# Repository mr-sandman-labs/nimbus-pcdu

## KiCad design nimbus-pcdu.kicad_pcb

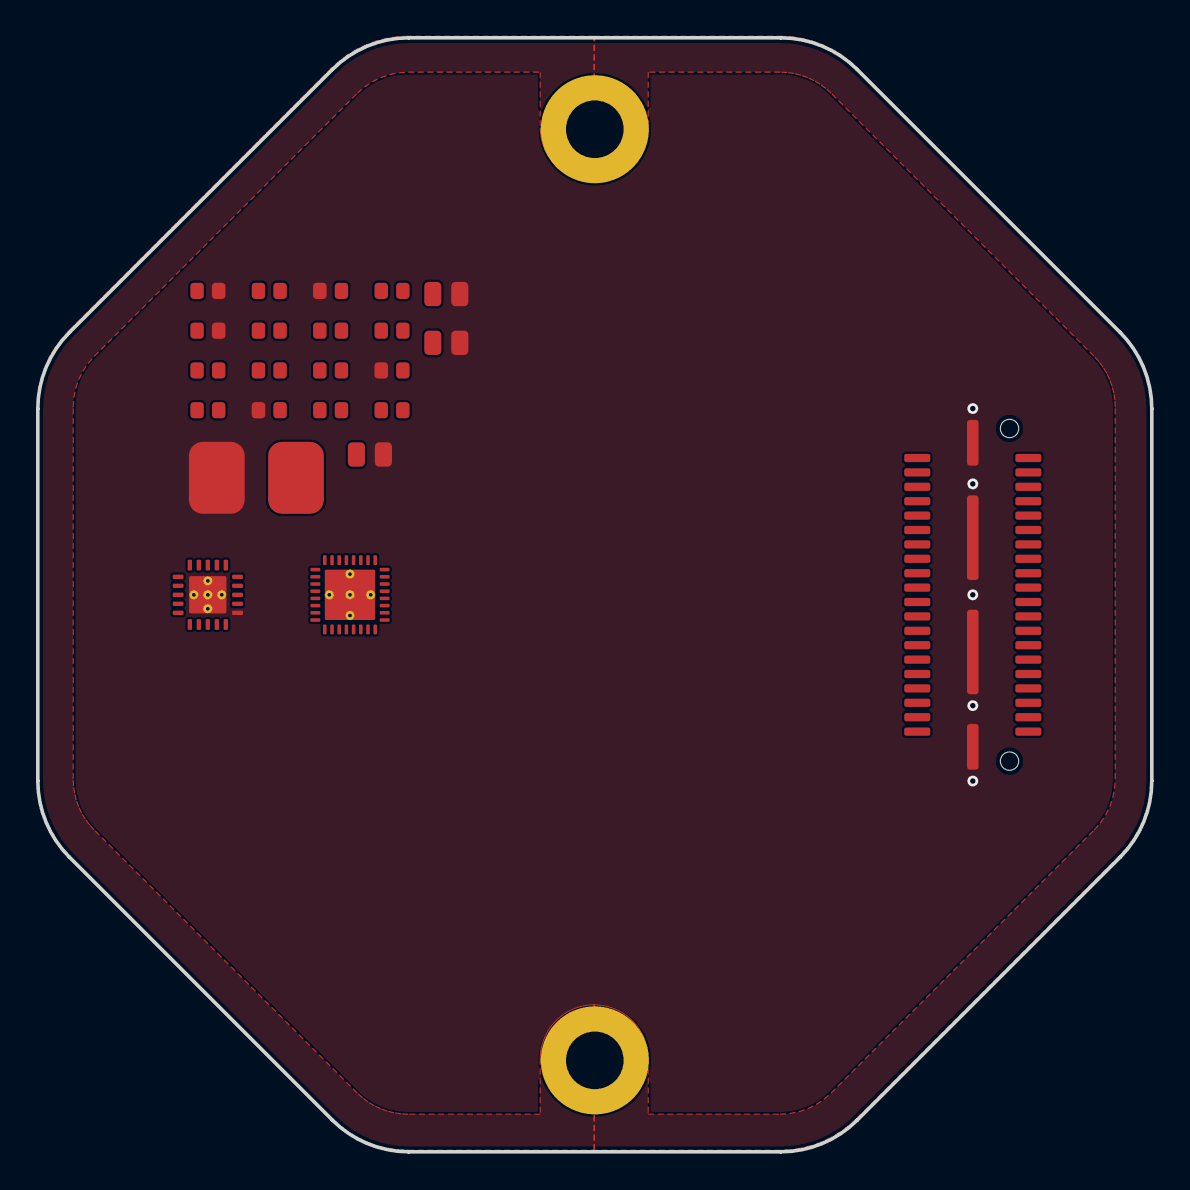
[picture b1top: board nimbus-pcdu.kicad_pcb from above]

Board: 4 copper layers, 61.9 x 61.9 mm, 23 parts (0 on the bottom side), 17 nets, no tracks yet.

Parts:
C1, C10, C11: 1μF; C_0805_Density_Least
C2, C3, C4, C5, C6: 220nF; C_0603_Density_Least
C7: 100nF; C_0603_Density_Least
C8, C9: 100pF; C_0603_Density_Least
J1: QTE-020-03-L-D-A
R1, R2, R3, R4, R5: 10Ω; R_0603_Density_Least
R6, R7, R8: 100Ω; R_0603_Density_Least
R9: 1mΩ; CRE2512-FZ-R001E-2
U1: BQ76905RGRR
U2: BQ25730RSNR

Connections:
+3.3V: J1.5, J1.6
+5V: J1.3, J1.4
/I2C1_SCL: J1.31, U1.12 (SCL)
/I2C1_SDA: J1.29, U1.13 (SDA)
GND: C1.2, C2.2, C3.2, C9.1, C10.2, C11.2, J1.G1, J1.G2, J1.G3, J1.G4, R1.1, R7.1, R9.1, U1.11 (VSS), U1.21 (EP)
unnamed: R8.1, R9.2
unnamed: C1.1, C9.2, R6.2, U1.17 (BAT)
unnamed: C11.1, U1.15 (REGOUT)
unnamed: C10.1, U1.16 (REGSRC)
unnamed: C7.2, C8.2, R8.2, U1.7 (SRN)
unnamed: C7.1, C8.1, R7.2, U1.6 (SRP)
unnamed: C3.1, R1.2, U1.5 (VC0)
unnamed: C2.1, C4.2, R2.2, U1.4 (VC1)
unnamed: C4.1, C5.2, R4.2, U1.1 (VC3A), U1.2 (VC3B), U1.3 (VC2)
unnamed: C5.1, C6.2, R3.2, U1.19 (VC4A), U1.20 (VC4B)
unnamed: C6.1, R5.2, U1.18 (VC5)
VBAT: J1.1, J1.2, R5.1

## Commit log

2025-12-31 Add kicad-library
2025-12-31 Add LICENSE and README
2025-12-31 Add .gitignore
2025-12-31 Setup KiCAD project
2026-01-03 Update kicad-library
2026-01-03 FInish setting up KiCAD project files
2026-01-03 Add workflows and README
2026-01-03 Add ability to update board images via GitHub UI
2026-01-03 Update board images
2026-01-03 Add interboard connector, mounting holes and BMS IC. Chassis connection still missing
2026-01-04 Add User.Drawings layer to PCB PDF
2026-01-04 Add initial BMS component selection

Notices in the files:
parts and their libraries:
LICENSE: CERN-OHL-S
